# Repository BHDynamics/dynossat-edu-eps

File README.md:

# DynOSSAT-EDU-EPS (Electric Power System)
DynOSSAT-EDU is the first open source PocketQube educational kit compatible with CircuitPython and Arduino.

This plaform is equipped with all the necessary modules for the operation of a nanosatellite (PocketQube)
in Low Earth Orbit (LEO) that would serve as a device for teaching, training, and driving curiosity about the philosophy and technology related to NewSpace.

This repository contains the hardware files for the EPS (Electric Power System), the module responsible for battery management and power distribution subsystems,
including charging through solar panels using flight-proven MPPT electronics.

Hardware in this repository is licenced under **CERN OHL v1.2**.

## Technical details

- Well-known 48 MHz Cortex-M0 ATSAMD21E18 MCU with 256 KB flash + 32 KB RAM
- 32 Mbit SPI flash for storing CircuitPython code and libraries
- Flight-proven SPV1040 Maximum Power Point Tracking (MPPT) IC for solar cells power management
- Ultra low input voltage L6924D Lithium battery charger management IC optimized for pairing with the SPV1040
- Separate 5V and 3.3V power rails generated through high-performance DC/DC converters
- Battery Current/Voltage/Power measurement through the flight-proven INA226 digital meter
- Back-powering protection and load switching through the TPS22918, member of a flight-proven family of switches
- User-controllable WS2812B addressable RGB LED
- Female USB-C 2.0 connector for power and data logging
- Standard Molex Picoblade 1.5 mm connectors for battery and solar cells
- Connected to the OBC through SPI/I2C/UART for data communication and/or redundancy

## Documentation

Available in this repo's [Wiki](https://github.com/BHDynamics/dynossat-edu-eps/wiki).

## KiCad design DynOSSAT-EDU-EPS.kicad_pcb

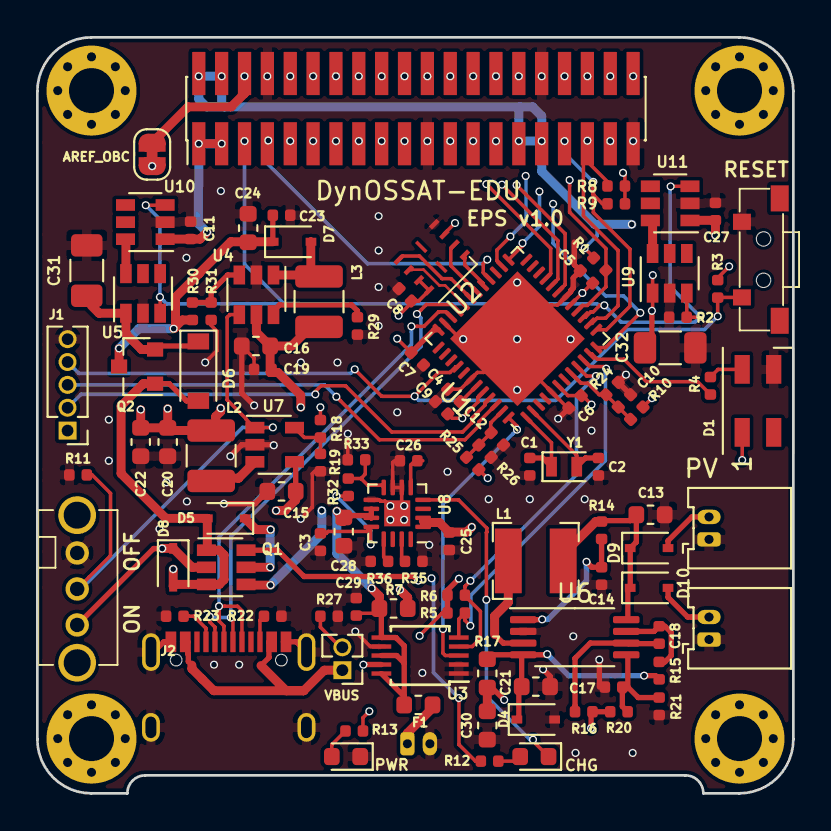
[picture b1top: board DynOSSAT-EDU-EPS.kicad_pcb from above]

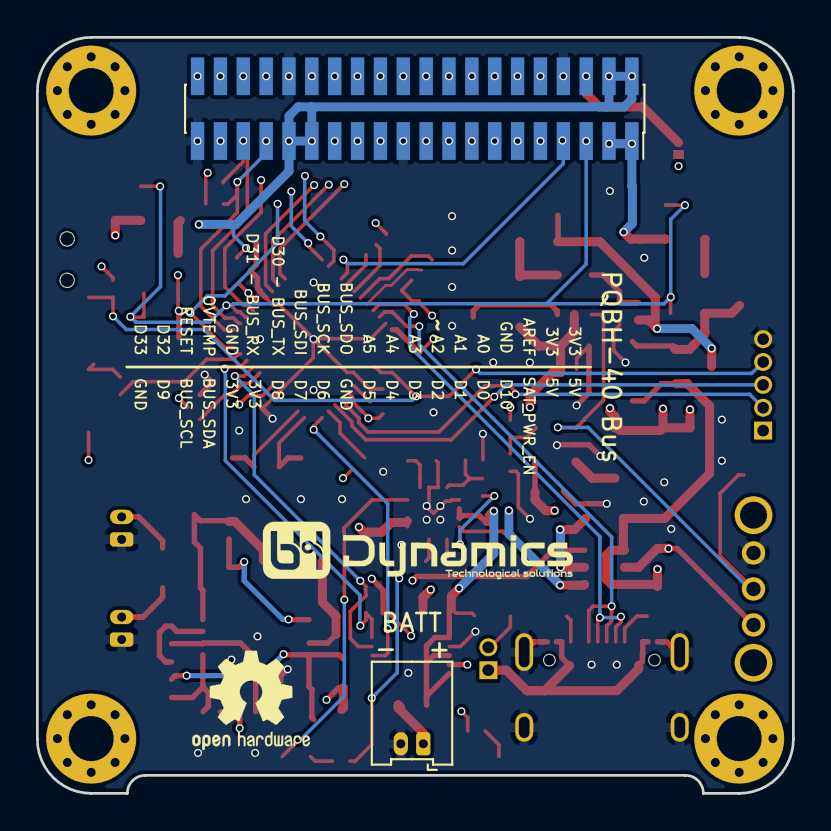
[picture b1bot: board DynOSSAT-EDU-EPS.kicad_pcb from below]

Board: 4 copper layers, 42.0 x 42.0 mm, 105 parts (2 on the bottom side), 90 nets.

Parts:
C1, C2: 22pF; C_0402_1005Metric
C3, C17: 1nF; C_0402_1005Metric
C4, C5, C6, C7, C8, C9, C14, C19, C23, C29: 100nF; C_0402_1005Metric
C10, C12, C26: 10nF; C_0402_1005Metric
C11, C18, C25, C27: 1uF; C_0402_1005Metric
C13, C30: 10uF; C_0603_1608Metric
C15, C16, C20, C22, C24: 22uF; C_0603_1608Metric
C21: 4.7F; C_0603_1608Metric
C28: 1uF; C_0603_1608Metric
C31, C32: 220uF; C_1206_3216Metric
D1: WS2812B; LED_SK6812MINI_PLCC4_3.5x3.5mm_P1.75mm
D2, D3: LED_Small; LED_0603_1608Metric
D4: 5V; D_SOD-323
D5, D7, D8, D9, D10: D_Schottky_Small; D_SOD-323
D6: D_Schottky_Small; D_SOD-123
F1: Fuse_3A; Fuse_0603_1608Metric
J1: Conn_01x05_Female; PinHeader_1x05_P1.27mm_Vertical
J2: USB_C_Receptacle_USB2.0; U262-161N-4BVC11
J4: PV Panel 1; Molex_PicoBlade_53048-0210_1x02_P1.25mm_Horizontal
J5: PV Panel 2; Molex_PicoBlade_53048-0210_1x02_P1.25mm_Horizontal
J6: Battery; Molex_PicoBlade_53048-0210_1x02_P1.25mm_Horizontal
J7: Conn_02x20_Odd_Even; PinHeader_2x20_P1.27mm_Vertical_SMD
J8: Conn_02x20_Odd_Even; PinSocket_2x20_P1.27mm_Vertical_SMD
JP1: Jumper; PinHeader_1x02_P1.27mm_Vertical
JP2: Jumper; SolderJumper-2_P1.3mm_Bridged_RoundedPad1.0x1.5mm
L1: 22uH; L_Bourns-SRN4018
L2: 2.2uH; L_1210_3225Metric
L3: 3.3uH; L_1210_3225Metric
Q1: SQ3989EV; SOT-23-6
Q2: DMG2305; SOT-23
R1, R2, R3, R11, R18, R27, R32: 100k; R_0402_1005Metric
R4: 510R; R_0402_1005Metric
R5, R6: 10k; R_0402_1005Metric
R7: 0.002R; R_0603_1608Metric
R8, R9, R29, R33: 47k; R_0402_1005Metric
R10, R25: 1M; R_0402_1005Metric
R12, R13: 330R; R_0402_1005Metric
R14, R15, R16: 1k; R_0402_1005Metric
R17: 0.033R; R_0603_1608Metric
R19: 22k2; R_0402_1005Metric
R20: 2.2M; R_0402_1005Metric
R21: 820k; R_0402_1005Metric
R22, R23: 5.1k; R_0402_1005Metric
R24: 10M; R_0402_1005Metric
R26: 1.5M; R_0402_1005Metric
R30: 88k; R_0402_1005Metric
R31, R35: 12k; R_0402_1005Metric
R36: 3k3; R_0402_1005Metric
SW1: SW_Push; 1TS002G-1800-3500-CT
SW2: SW_SPDT; OS102011MA1QN1
U1: ATSAMD21G18A; QFN-48-1EP_7x7mm_P0.5mm_EP5.3x5.3mm
U2: GD25Q32; WSON-8-1EP_3x4mm_P0.8mm
U3: INA226; TSSOP-10_3x3mm_P0.5mm
U4: FP6291; SOT-23-6
U5, U9, U10, U11: TPS22918; SOT-23-6
U6: SPV1040; TSSOP-8_4.4x3mm_P0.65mm
U7: SY8089; SOT-23-5
U8: L6924D; VQFN-16-1EP_3x3mm_P0.5mm_EP1.45x1.45mm
Y1: 32.768 kHz - 12.5pF; Crystal_SMD_2012-2Pin_2.0x1.2mm

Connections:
+3V3_EPS: C5.1, C6.1, C7.1, C8.1, C9.1, C20.1, C22.1, C32.1, D1.1, J1.1, L2.2, R3.1, R5.1, R6.1, R8.1, R9.1, R13.2, R18.2, U1.6, U1.17, U1.36, U1.44, U2.3, U2.7, U2.8, U9.1
+3V3_SAT: C27.1, J7.2, J7.4, J7.29, J7.31, J8.2, J8.4, J8.29, J8.31, JP2.1, R1.1, R10.1, U11.1
+5V_EPS: C31.1, D6.1, Q2.2, U5.1
+5V_SAT: C11.1, J7.1, J7.3, J8.1, J8.3, R25.1, U10.1
+BATT: C28.1, C29.1, F1.2, R7.1, U3.6, U3.8, U3.10, U8.10, U8.11
+BATT_MON: C16.1, C19.1, L3.1, Q1.4, R7.2, U3.9, U4.5
/3V3_MEAS: C10.1, R10.2, R24.1, U1.8
/5V_MEAS: C12.1, R25.2, R26.1, U1.47
/CS_FLASH: U1.29, U2.1
/Connectors/A0_OBC: J7.10, J8.10
/Connectors/A1_OBC: J7.12, J8.12
/Connectors/A2_OBC: J7.14, J8.14
/Connectors/A3_OBC: J7.16, J8.16
/Connectors/A4_OBC: J7.18, J8.18
/Connectors/A5_OBC: J7.20, J8.20
/Connectors/D0_OBC: J7.9, J8.9
/Connectors/D1_OBC: J7.11, J8.11
/Connectors/D2_OBC: J7.13, J8.13
/Connectors/D3_OBC: J7.15, J8.15
/Connectors/D4_OBC: J7.17, J8.17
/Connectors/D5_OBC: J7.19, J8.19
/Connectors/D6_OBC: J7.23, J8.23
/Connectors/D7_OBC: J7.25, J8.25
/Connectors/D8_OBC: J7.27, J8.27
/Connectors/D9_OBC: J7.37, J8.37
/Connectors/OBC_SWDCLK: J7.38, J8.38
/Connectors/OBC_SWDIO: J7.40, J8.40
/Power/5V_BATT: C23.1, C24.1, D7.1, Q2.3, R30.2
/Power/ST1: D2.1, U8.4
/Power/TH: R32.2, R33.1, U8.8
/Power/VCHARGE: C25.1, D5.1, Q1.5, R12.2, U8.1, U8.2
/Power/VOUT_PV: C30.1, Q1.6, R16.1, R17.1, R20.2
/Power/VREF: C3.1, R32.1, U8.12
/Power/VSYS: C15.1, D8.1, Q1.2, SW2.3, U7.4
/RGB: R4.2, U1.11
/SCK_FLASH: U1.32, U2.6
/SDI_FLASH: U1.30, U2.2
/SDO_FLASH: U1.31, U2.5
AREF_SAT: J7.6, J8.6, JP2.2
EPS_PWR_EN: R11.2, SW2.2, U4.4, U7.1
EPS_SWCLK: J1.2, U1.45
EPS_SWDIO: J1.3, U1.46
EPS_nRST: J1.4, R3.2, SW1.1, U1.40
GND: C1.2, C2.2, C3.2, C4.2, C5.2, C6.2, C7.2, C8.2, C9.2, C10.2, C11.2, C12.2, C13.2, C14.2, C15.2, C16.2, C17.2, C19.2, C20.2, C21.2, C22.2, C23.2, C24.2, C25.2, C26.2, C27.2, C28.2, C29.2, C30.2, C31.2, C32.2, D1.3, D3.1, D4.2, J1.5, J2.A1, J2.A12, J2.B1, J2.B12, J2.S1, J4.1, J5.1, J6.2, J7.8, J7.21, J7.32, J7.39, J8.8, J8.21, J8.32, J8.39, R2.2, R11.1, R19.1, R21.1, R22.2, R23.2, R24.2, R26.2, R27.2, R29.1, R31.1, R33.2, R35.2, R36.2, SW1.2, SW2.1, U1.5, U1.18, U1.35, U1.42, U1.49, U2.4, U3.1, U3.2, U3.7, U4.2, U5.2, U6.2, U7.2, U8.6, U8.7, U8.9, U8.17, U9.2, U10.2, U11.2
I2C_BUS_SCL: J7.35, J8.35, R8.2, U1.14
I2C_BUS_SDA: J7.33, J8.33, R9.2, U1.13
INT_IMU_OBC: J7.7, J8.7, U1.28
unnamed: C1.1, U1.1, Y1.1
unnamed: C2.1, U1.2, Y1.2
unnamed: C4.1, U1.43
unnamed: C14.1, R14.1, U6.1
unnamed: C17.1, R20.1, R21.2, U6.5
unnamed: C18.1, R15.2, U6.7
unnamed: C18.2, R16.2, U6.6
unnamed: C21.1, D4.1, R15.1, R17.2, U6.4
unnamed: C26.1, U8.5
unnamed: D1.4, R4.1
unnamed: D2.2, R12.1
unnamed: D3.2, R13.1
unnamed: D7.2, L3.2, U4.1
unnamed: D9.2, J5.2
unnamed: D10.2, J4.2
unnamed: F1.1, J6.1
unnamed: J2.A5, R23.1
unnamed: J2.B5, R22.1
unnamed: L1.2, U6.3
unnamed: L2.1, U7.3
unnamed: R18.1, R19.2, U7.5
unnamed: R29.2, U4.6
unnamed: R30.1, R31.2, U4.3
unnamed: R35.1, U8.15
unnamed: R36.1, U8.13
unnamed: U5.6, U10.6
unnamed: U9.6, U11.6
OBC_OVTEMP: J7.34, J8.34, U1.12
OBC_RX: J7.30, J8.30, U1.25
OBC_TX: J7.28, J8.28, U1.26
PV: C13.1, D9.1, D10.1, L1.1, R14.2, U6.8
PWRMON_ALERT: U1.48, U3.3
PWRMON_SCL: R5.2, U1.10, U3.5
PWRMON_SDA: R6.2, U1.9, U3.4
SAT_PWR_EN: J7.5, J8.5, R2.1, U1.15, U5.3, U9.3, U10.3, U11.3
SAT_nRST: J7.36, J8.36, R1.2, U1.16
SPI_BUS_SCK: J7.24, J8.24, U1.20
SPI_BUS_SDI: J7.26, J8.26, U1.19
SPI_BUS_SDO: J7.22, J8.22, U1.21
USB_D+: J2.A6, J2.B6, U1.34
USB_D-: J2.A7, J2.B7, U1.33
VBUS: J2.A4, J2.A9, J2.B4, J2.B9, JP1.1
VBUS_JMP: D5.2, D6.2, D8.2, JP1.2, Q1.1, Q1.3, Q2.1, R27.1

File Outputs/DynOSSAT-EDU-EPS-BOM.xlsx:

Item | Qty | Reference(s) | Value | Part Number | Comments
1 | 2 | C1, C2 | 22pF |  | 0402 NP0 22pF
2 | 2 | C3, C17 | 1nF |  | 0402 NP0 1nF
3 | 10 | C4, C5, C6, C7, C8, C9, C14, C19, C23, C29 | 100nF |  | 0402 X7R/X5R 100nF
4 | 3 | C10, C12, C26 | 10nF |  | 0402 X7r/X5R 100nF
5 | 4 | C11, C18, C25, C27 | 1uF |  | 0402 1uF 10V or greater X5R or better
6 | 2 | C13, C30 | 10uF |  | 0603 10uF 10V or greater X5R or better
7 | 5 | C15, C16, C20, C22, C24 | 22uF |  | 0603 22uF 10V or greater X5R or better
8 | 1 | C21 | 4.7uF |  | 0603 4.7uF 10V or greater X5R or better
9 | 1 | C28 | 1uF |  | 0603 1uF 10V or greater X5R or better
10 | 2 | C31, C32 | 220uF | GRM31CR60J227ME11L | 1206 6.3V 220 uF
11 | 1 | D1 | WS2812B-MINI | WS2812B-MINI | RGB LED
12 | 2 | D2, D3 | LED_Small |  | 0603 LED. D2 Red, D3 Green
13 | 1 | D4 | LED_Small | SD05-01FTG | 5V TVS Diode SOD-323
14 | 5 | D5, D7, D8, D9, D10 | D_Schottky_Small | CUS10S30,H3F | Diode_SMD:D_SOD-323
15 | 1 | D6 | D_Schottky_Small | 1N5819HWQ-7-F | Diode_SMD:D_SOD-123
16 | 1 | F1 | Fuse_3A | T0603FF3000TM | Fuse:Fuse_0603_1608Metric
17 | 1 | J1 | Conn_01x05_Female | - | Connector_PinHeader_1.27mm:PinHeader_1x05_P1.27mm_Vertical
18 | 1 | J2 | USB_C_Receptacle_USB2.0 | U262-161N-4BVC11 | DynOSSAT:U262-161N-4BVC11
19 | 1 | J4 | PV Panel 1 | 53048-0210 | Connector_Molex:Molex_PicoBlade_53048-0210_1x02_P1.25mm_Horizontal
20 | 1 | J5 | PV Panel 2 | 53048-0210 | Connector_Molex:Molex_PicoBlade_53048-0210_1x02_P1.25mm_Horizontal
21 | 1 | J6 | Battery | 53048-0210 | Connector_Molex:Molex_PicoBlade_53048-0210_1x02_P1.25mm_Horizontal
22 | 1 | J7 | Main Bus PQBH40 | We don't have part numbers. Use generic brand | Pin header male 1.27mm pitch 2x20 vertical SMD
23 | 1 | J8 | Main Bus PQBH40 | We don't have part numbers. Use generic brand | Pin socket female 1.27mm pitch 2x20 vertical SMD
24 | 1 | JP1 | Jumper | We don't have part numbers. Use generic brand | Pin header male 1.27mm pitch 1x02 Vertical Through-Hole
25 | 1 | JP2 | Jumper | - | Solder jumper
26 | 1 | L1 | 22uH | SMNR4030-220MT | Inductor_SMD:L_Bourns-SRN4018
27 | 1 | L2 | 2.2uH | LQH32PN2R2NN0L | 1210 2.2uH Power Inductor
28 | 1 | L3 | 3.3uH | LQH32PN3R3NN0L | 1210 3.3uH Power Inductor
29 | 1 | Q1 | SQ3989EV | SQ3989EV-T1_GE3 | Dual P-Channel Mosfet
30 | 1 | Q2 | DMG2305 | DMG2305UX-7 | P-Channel Power Mosfet
31 | 7 | R1, R2, R3, R11, R18, R27, R32 | 100k |  | 0402 100k 1%
32 | 1 | R4 | 510R |  | 0402 510R 1%
33 | 2 | R5, R6 | 10k |  | 0402 10k 1%
34 | 1 | R7 | 0.002R | LVT06R0020HER | 0603 0.002R Current Shunt
35 | 2 | R10, R25 | 1M |  | 0402 1M
36 | 2 | R12, R13 | 330R |  | 0402 330R
37 | 3 | R14, R15, R16 | 1k |  | 0402 1k
38 | 1 | R17 | 0.033R | WSL0603R0330FEA | 0603 0.033R Current Shunt
39 | 1 | R19 | 22k2 |  | 0402 22.2k
40 | 1 | R20 | 2.2M |  | 0402 2.2M
41 | 1 | R21 | 820k |  | 0402 820k
42 | 2 | R22, R23 | 5.1k |  | 0402 5.1k
43 | 1 | R24 | 10M |  | 0402 10M
44 | 1 | R26 | 1.5M |  | 0402 1.5M
45 | 4 | R8, R9, R29, R33 | 47k |  | 0402 47k
46 | 1 | R30 | 88k |  | 0402 88k
47 | 2 | R31, R35 | 12k |  | 0402 12k
48 | 1 | R36 | 3k3 |  | 0402 3k3
49 | 1 | SW1 | SW_Push | 1TS002G-1800-3500-CT | Push Button side mount
50 | 1 | SW2 | SW_SPDT | OS102011MA1QN1 | SPDT switch
51 | 1 | U1 | ATSAMD21G18A | ATSAMD21G18A-MUT | MCU
52 | 1 | U2 | GD25Q32 | GD25Q32CNIGR | 32 Mbit flash memory SPI
53 | 1 | U3 | INA226 | INA226AIDGSR | Current/Voltage monitoring IC
54 | 1 | U4 | FP6291 | FP6291LR-G1 | Step-Up 2A DC-DC Boost Converter
55 | 4 | U5, U9, U10, U11 | TPS22918 | TPS22918DBVR | Load Switch
56 | 1 | U6 | SPV1040 | SPV1040T | Solar Power Harvester
57 | 1 | U7 | SY8089 | SY8089AAC | Step-Down 2A DC-DC Buck Converter
58 | 1 | U8 | L6924D | L6924D | Low Vin Battery Charger IC
59 | 1 | Y1 | 32.768 kHz - 12.5pF | X201232768KGD2SI | 2012 32768 kHz Crystal 12.5pF
For passives (resistors, capacitors, etc) you may use any quality brand while m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

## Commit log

2020-10-15 First commit RC 1.0
2020-10-16 Add README and LICENCE
2020-11-06 Change MISO/MOSI for SDI/SDO
    Update library to latest version
